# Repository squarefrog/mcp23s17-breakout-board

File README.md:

# MCP23S17 Breakout Board

A 30x40mm breakout board for the [MCP23S17](http://www.microchip.com/wwwproducts/en/MCP23S17) SOIC package.

As used in my [MIDI Encoder Box](https://github.com/squarefrog/teensy-midi-encoder-box) project.

## Assembly

1. Start by soldering the MCP23S17 chip onto the board. Ensure you note the position of pin 1 by looking for the dot on the board and the chip.

2. **NOTE:** before proceeding any further, consider what you'd like the hardware address of the chip to be. There are 3 solder jumpers at the top of the board. You may use these to assign an address to the chip. Connect the middle pin of `A0`, `A1`, `A2`, to either ground (labelled `0`), or VDD (labelled `1`). Simply use some solder to join the two pads together.

3. Next, solder on the 2 1x8 header pins. Solder one edge pin first, then check that the header is straight. Once you're happy the header is straight solder the rest of the pins.

4. Now do the same for the 2 1x2 interrupt and power pins.

5. Finally, solder the 2 1x4 SPI header pins in place. Optionally, you may want to use 1x6 headers and get an extra few ground connections.

## IMPORTANT

Ensure you don't forget to solder the jumper pads. Even if you don't plan to use hardware addressing, you should bridge between the middle pin and ground pin.

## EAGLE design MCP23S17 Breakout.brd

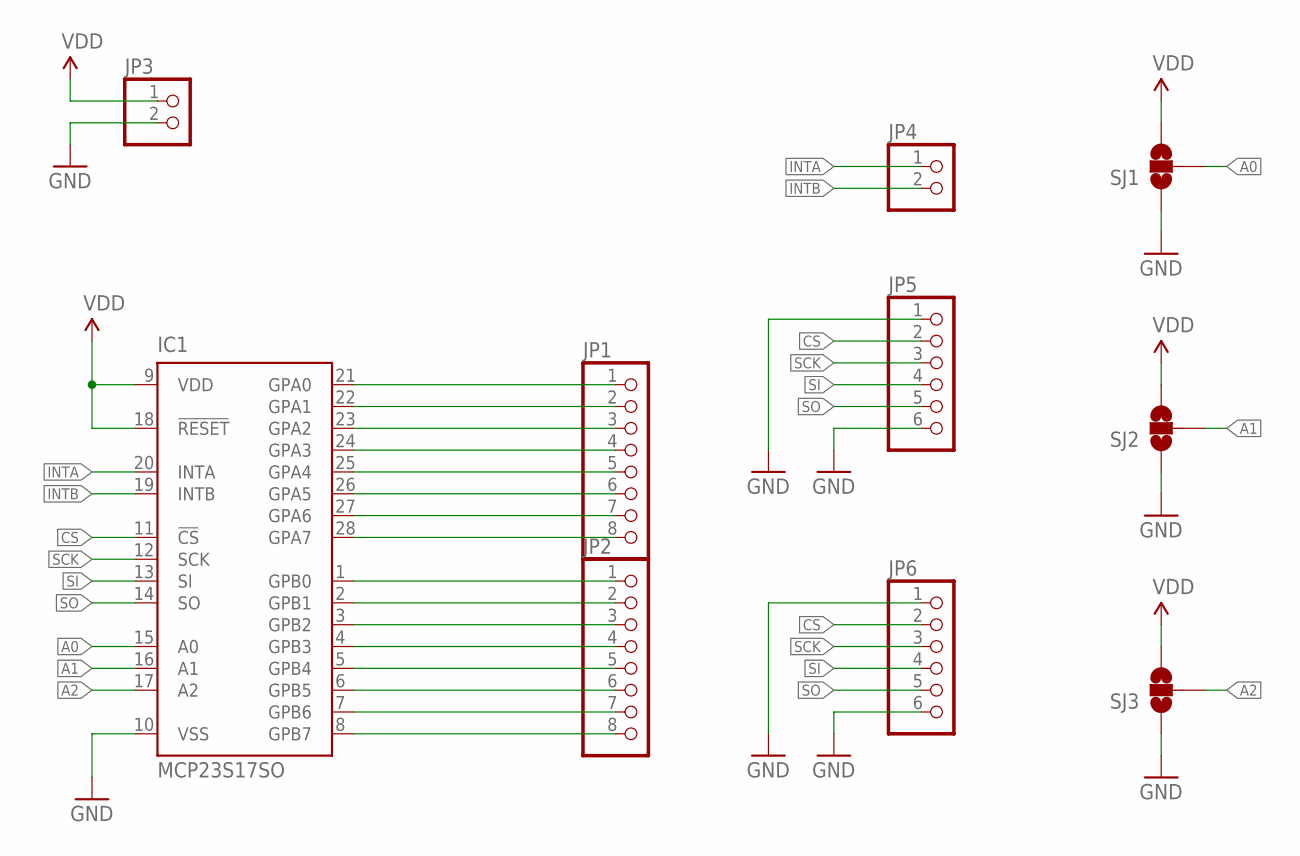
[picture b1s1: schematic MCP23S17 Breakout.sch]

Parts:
IC1: MCP23S17SO; SO28W
JP1, JP2: PINHD-1X8; 1X08
JP3, JP4: PINHD-1X2; 1X02
JP5, JP6: PINHD-1X6; 1X06
SJ1, SJ2, SJ3: SOLDERJUMPER_2WAYT; SJ_2

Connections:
3.3V: IC1.9 (VDD), IC1.18 (!RESET), JP3.1, SJ1.3, SJ2.3, SJ3.3
A0: IC1.15 (A0), SJ1.2
A1: IC1.16 (A1), SJ2.2
A2: IC1.17 (A2), SJ3.2
CS: IC1.11 (!CS), JP5.2, JP6.2
GND: IC1.10 (VSS), JP3.2, JP5.1, JP5.6, JP6.1, JP6.6, SJ1.1, SJ2.1, SJ3.1
INTA: IC1.20 (INTA), JP4.1
INTB: IC1.19 (INTB), JP4.2
unnamed: IC1.21 (GPA0), JP1.1
unnamed: IC1.22 (GPA1), JP1.2
unnamed: IC1.23 (GPA2), JP1.3
unnamed: IC1.24 (GPA3), JP1.4
unnamed: IC1.25 (GPA4), JP1.5
unnamed: IC1.26 (GPA5), JP1.6
unnamed: IC1.27 (GPA6), JP1.7
unnamed: IC1.28 (GPA7), JP1.8
unnamed: IC1.1 (GPB0), JP2.1
unnamed: IC1.2 (GPB1), JP2.2
unnamed: IC1.3 (GPB2), JP2.3
unnamed: IC1.4 (GPB3), JP2.4
unnamed: IC1.5 (GPB4), JP2.5
unnamed: IC1.6 (GPB5), JP2.6
unnamed: IC1.7 (GPB6), JP2.7
unnamed: IC1.8 (GPB7), JP2.8
SCK: IC1.12 (SCK), JP5.3, JP6.3
SI: IC1.13 (SI), JP5.4, JP6.4
SO: IC1.14 (SO), JP5.5, JP6.5

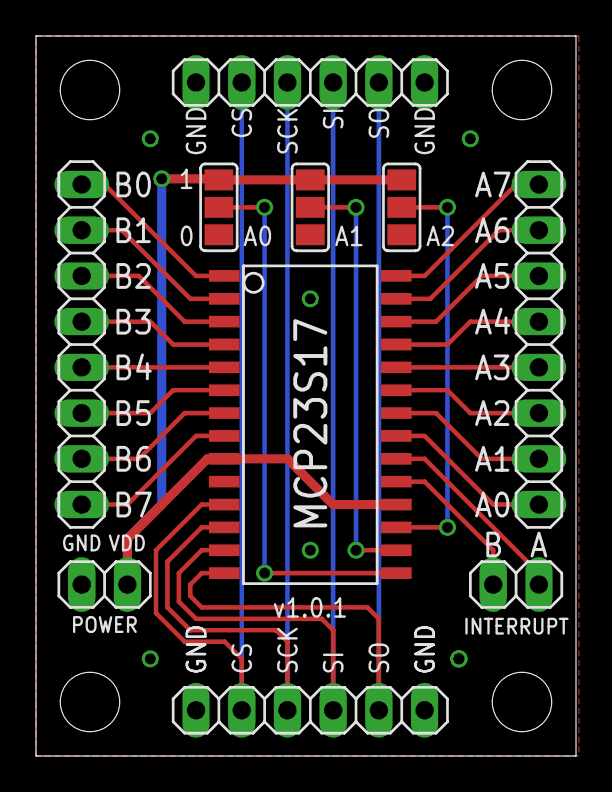
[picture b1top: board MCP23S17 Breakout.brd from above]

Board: 2 copper layers, 30.0 x 40.0 mm, 14 parts (0 on the bottom side), 27 nets.

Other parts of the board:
U$1, U$2, U$3, U$4: STAND-OFF

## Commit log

2016-08-20 Add images
2016-08-20 Add assembly instructions.
2016-08-24 Update breakout
2016-08-24 Update font sizes

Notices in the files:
MCP23S17 Breakout.brd:
CC BY-SA 4.0
parts and their libraries:
SparkFun-Retired: Licensing:Creative Commons ShareAlike 4.0 International - https://creativecommons.org/licenses/by-sa/4.0
